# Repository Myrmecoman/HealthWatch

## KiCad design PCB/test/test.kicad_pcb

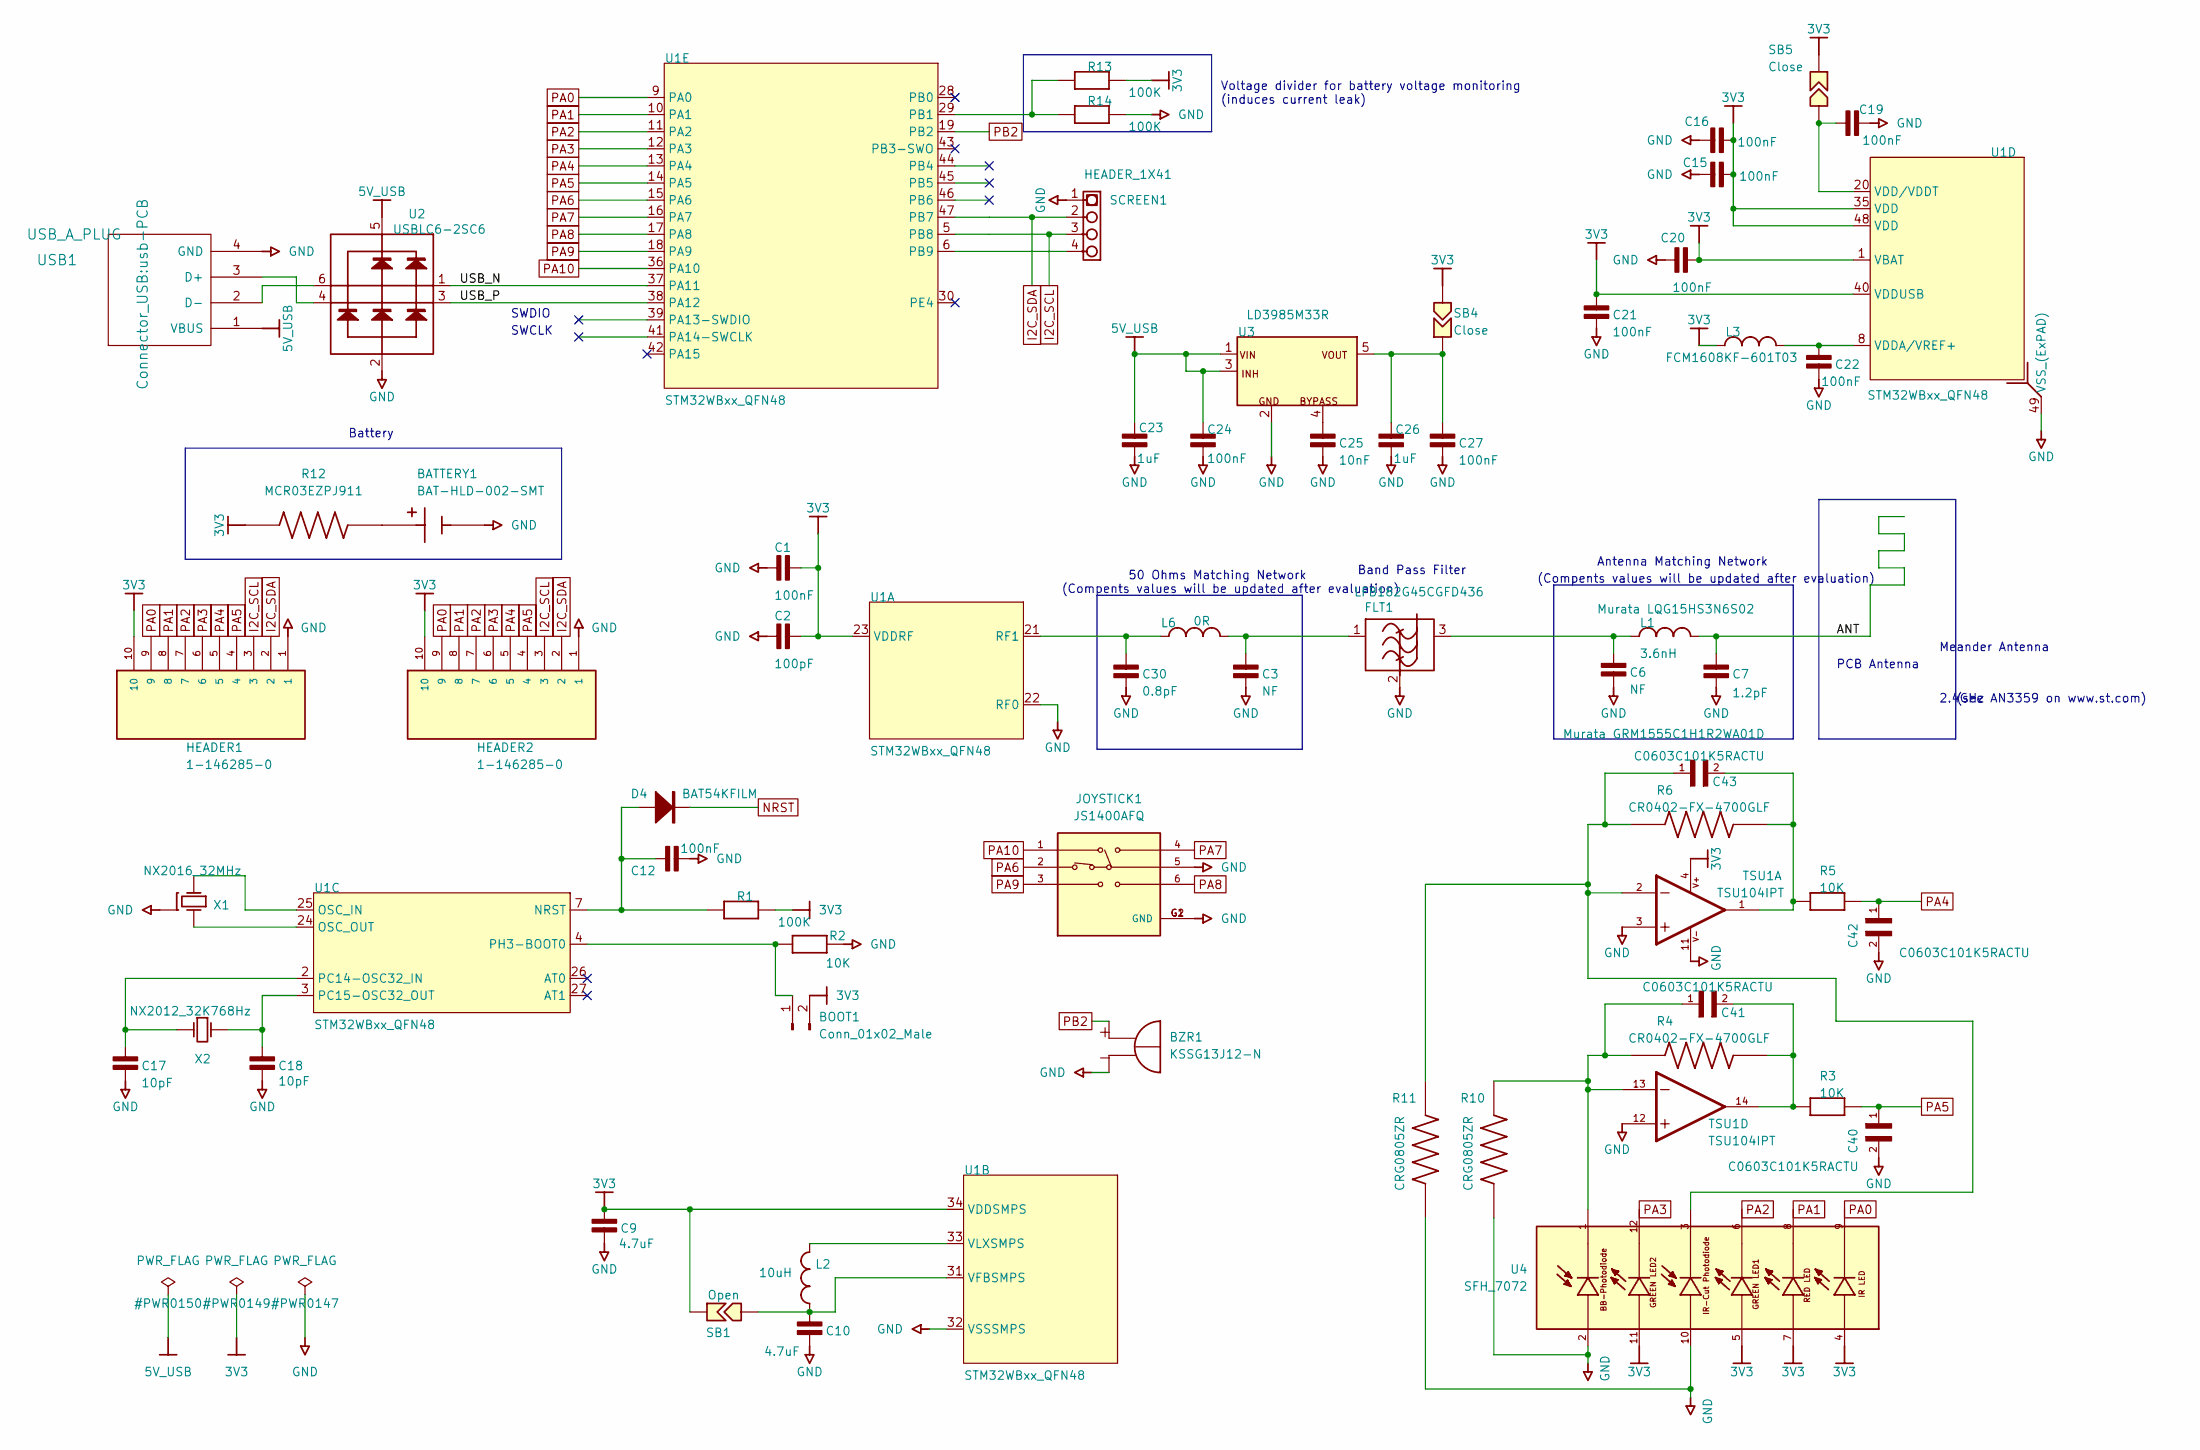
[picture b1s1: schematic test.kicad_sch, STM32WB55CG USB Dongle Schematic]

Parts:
BATTERY1: BAT-HLD-002-SMT; BAT_BAT-HLD-002-SMT; PARTREV B
BOOT1: Conn_01x02_Male; PinHeader_1x02_P2.54mm_Vertical
BZR1: KSSG13J12-N; XDCR_KSSG13J12-N; PARTREV 1.4
C1, C12, C15, C16, C19, C20, C21, C22, C24, C27: 100nF; 0402_CAP_NPOL
C2: 100pF; 0402_CAP_NPOL
C3, C6: NF; 0402_CAP_NPOL
C7: 1.2pF; 0402_CAP_NPOL
C9, C10: 4.7uF; 0402_CAP_NPOL
C17, C18: 10pF; 0402_CAP_NPOL
C23, C26: 1uF; 0603_CAP_NPOL
C25: 10nF; 0402_CAP_NPOL
C30: 0.8pF; 0402_CAP_NPOL
C40, C41, C42, C43: C0603C101K5RACTU; CAPC1608X87N
D4: BAT54KFILM; SOD523
FLT1: LFB182G45CGFD436
HEADER1, HEADER2: 1-146285-0; TE_1-146285-0
JOYSTICK1: JS1400AFQ; SW_JS1400AFQ; PARTREV C
L1: 3.6nH; 0402_COIL
L2: 10uH; 0805_COIL
L3: FCM1608KF-601T03; 0603_COIL
L6: 0R; 0402_COIL
R1, R13, R14: 100K; 0402_RES
R2, R3, R5: 10K; 0402_RES
R4, R6: CR0402-FX-4700GLF; RESC1005X40N
R10, R11: CRG0805ZR; RESC2012X65N; Tolerance 0%; Voltage_Rating 150 V
R12: MCR03EZPJ911; RESC1608X55N
SB1: Open; SB-tiny
SB4, SB5: Close; SB-tiny
SCREEN1: HEADER_1X41; PinHeader_1x04_P2.54mm_Vertical
TSU1: TSU104IPT; SOP65P640X120-14N; PARTREV 3
U1: STM32WBxx_QFN48
U2: USBLC6-2SC6; SOT23-6
U3: LD3985M33R; SOT23-5; MANUFACTURER P/N LD3985M33R
U4: SFH_7072; XDCR_SFH_7072; PARTREV 1.0
USB1: USB_A_PLUG; usb-PCB
X1: NX2016_32MHz; NX2016_4P; MANUFACTURER P/N NX2016SA 32 MHz EXS00A-CS06654
X2: NX2012_32K768Hz; NX2012_2P; MANUFACTURER P/N NX2012SA 32.768KHz EXS00A-MU00389

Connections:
3V3: BOOT1.2, C1.2, C2.2, C9.1, C15.1, C16.1, C20.2, C21.2, HEADER1.10, HEADER2.10, L3.1, R1.1, R12.1, R13.1, SB1.2, SB4.1, SB5.2, TSU1.4, U1.1 (VBAT), U1.23 (VDDRF), U1.34 (VDDSMPS), U1.35 (VDD), U1.40 (VDDUSB), U1.48 (VDD), U4.4, U4.5, U4.7, U4.11
5V_USB: C23.2, C24.2, U2.5, U3.1 (VIN), U3.3 (CE), USB1.1 (VBUS)
/ANT: C7.2, L1.2
/USB_N: U1.37 (PA11), U2.1
/USB_P: U1.38 (PA12), U2.3
GND: BATTERY1.N, BZR1.N, C1.1, C2.1, C3.1, C6.2, C7.1, C9.2, C10.2, C12.2, C15.2, C16.2, C17.2, C18.2, C19.2, C20.1, C21.1, C22.2, C23.1, C24.1, C25.1, C26.1, C27.1, C30.1, C40.2, C42.2, FLT1.2 (GND), HEADER1.1, HEADER2.1, JOYSTICK1.5, JOYSTICK1.G1 (GND), JOYSTICK1.G2 (GND), R2.2, R10.2, R11.2, R14.1, SCREEN1.1, TSU1.3, TSU1.11, TSU1.12, U1.22 (RF0), U1.32 (VSSSMPS), U1.49 (VSS_(ExPAD)), U2.2, U3.2 (VSS), U4.2, U4.10, USB1.4 (GND), X1.2, X1.4
I2C_SCL: HEADER1.3, HEADER2.3, SCREEN1.3, U1.5 (PB8)
I2C_SDA: HEADER1.2, HEADER2.2, SCREEN1.2, U1.47 (PB7)
NRST: D4.K
unnamed: BATTERY1.P1, BATTERY1.P2, R12.2
unnamed: BOOT1.1, R2.1, U1.4 (PH3-BOOT0)
unnamed: C3.2, FLT1.1 (I/O), L6.2
unnamed: C6.1, FLT1.3 (I/O), L1.1
unnamed: C10.1, L2.1, SB1.1, U1.31 (VFBSMPS)
unnamed: C12.1, D4.A, R1.2, U1.7 (NRST)
unnamed: C17.1, U1.2 (PC14-OSC32_IN), X2.1 (OSC1)
unnamed: C18.1, U1.3 (PC15-OSC32_OUT), X2.2 (OSC2)
unnamed: C19.1, SB5.1, U1.20 (VDD/VDDT)
unnamed: C22.1, L3.2, U1.8 (VDDA/VREF+)
unnamed: C25.2, U3.4 (BYPASS)
unnamed: C26.2, C27.2, SB4.2, U3.5 (VOUT)
unnamed: C30.2, L6.1, U1.21 (RF1)
unnamed: C41.1, R4.1, R10.1, TSU1.13, U4.1
unnamed: C41.2, R3.1, R4.2, TSU1.14
unnamed: C43.1, R6.1, R11.1, TSU1.2, U4.3
unnamed: C43.2, R5.1, R6.2, TSU1.1
unnamed: L2.2, U1.33 (VLXSMPS)
unnamed: R13.2, R14.2, U1.29 (PB1)
unnamed: SCREEN1.4, U1.6 (PB9)
unnamed: U1.24 (OSC_OUT), X1.3 (OSC2)
unnamed: U1.25 (OSC_IN), X1.1 (OSC1)
unnamed: U2.4, USB1.3 (D+)
unnamed: U2.6, USB1.2 (D-)
PA0: HEADER1.9, HEADER2.9, U1.9 (PA0), U4.9
PA1: HEADER1.8, HEADER2.8, U1.10 (PA1), U4.8
PA2: HEADER1.7, HEADER2.7, U1.11 (PA2), U4.6
PA3: HEADER1.6, HEADER2.6, U1.12 (PA3), U4.12
PA4: C42.1, HEADER1.5, HEADER2.5, R5.2, U1.13 (PA4)
PA5: C40.1, HEADER1.4, HEADER2.4, R3.2, U1.14 (PA5)
PA6: JOYSTICK1.2, U1.15 (PA6)
PA7: JOYSTICK1.4, U1.16 (PA7)
PA8: JOYSTICK1.6, U1.17 (PA8)
PA9: JOYSTICK1.3, U1.18 (PA9)
PA10: JOYSTICK1.1, U1.36 (PA10)
PB2: BZR1.P, U1.19 (PB2)

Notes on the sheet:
(Compents values will be updated after evaluation)
Band Pass Filter
PCB Antenna
SWDIO
Antenna Matching Network
(see AN3359 on www.st.com)
2.4GHz
50 Ohms Matching Network
SWCLK
Meander Antenna
Battery
Voltage divider for battery voltage monitoring (induces current leak)

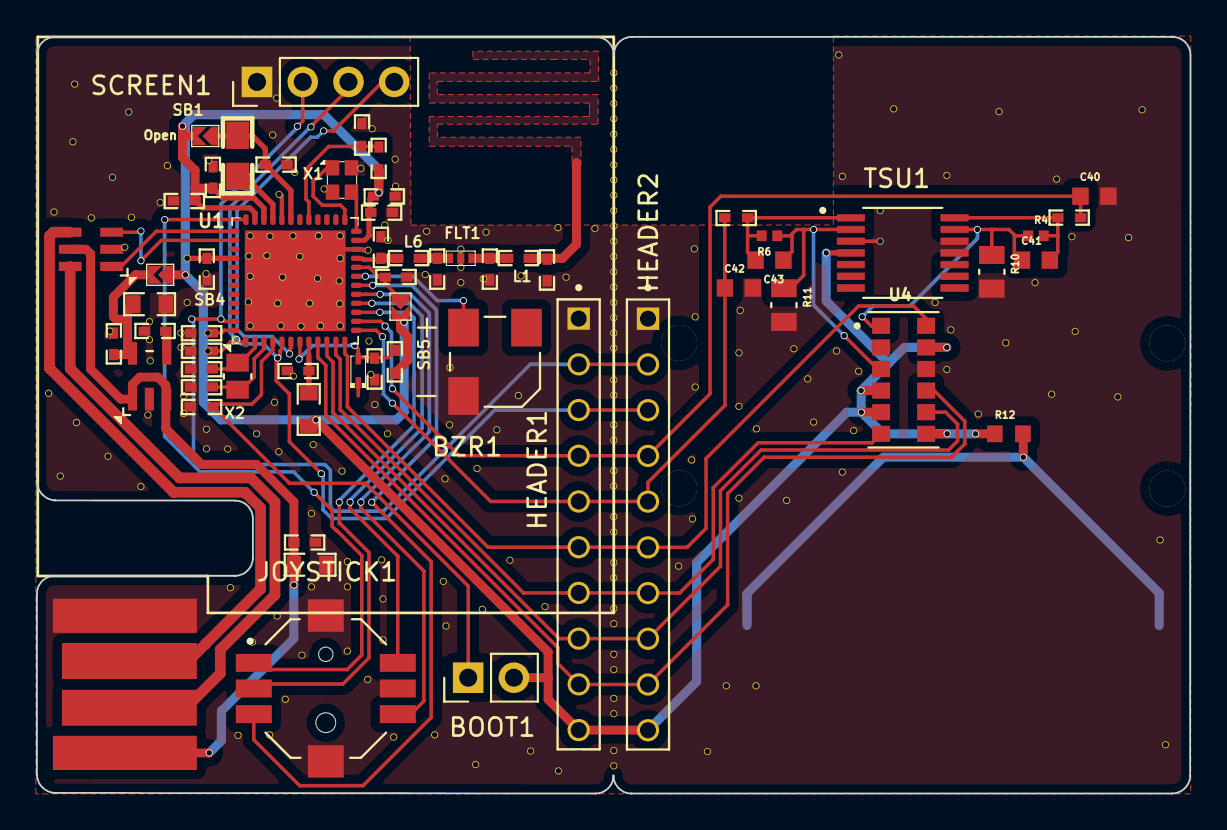
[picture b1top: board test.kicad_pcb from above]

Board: 2 copper layers, 64.1 x 42.0 mm, 61 parts (1 on the bottom side), 44 nets.

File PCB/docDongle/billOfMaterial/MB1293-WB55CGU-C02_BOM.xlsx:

|  |  |  | Bill of materials
 |  |  |  | Board reference: | MB1293
 |  |  |  | Variant: | ---
 |  |  |  | PCB revision: | C
 |  |  |  | Assembly revision: | 02
 |  |  |  | Date: | 14th November 2018
Designator | Description | Comment | FootPrint | Manufacturer | Manufacturer Part_Number | Fitted | Quantity | ECCN_EU | ECCN_US
C1, C12, C15, C16, C19, C20, C21, C22, C24, C27 | Capacitor_not polarized X7R | 100nF | 0402_CAP_NPOL |  |  | YES | 10 | NA | NA
C2 | Capacitor_not polarized | 100pF | 0402_CAP_NPOL |  |  | YES | 1 | NA | NA
C3 | Capacitor_not polarized | --- | 0402_CAP_NPOL |  |  | NO | 1 | NA | NA
C4, C25 | Capacitor_not polarized | 10nF | 0402_CAP_NPOL |  |  | YES | 2 | NA | NA
C8, C28, C29 | Capacitor_not polarized | --- | 0402_CAP_NPOL |  |  | NO | 3 | NA | NA
C6 | Capacitor_not polarized | --- | 0402_CAP_NPOL |  |  | NO | 1 | NA | NA
C7 | Capacitor_not polarized | 1.2pF | 0402_CAP_NPOL | MURATA | GRM1555C1H1R2WA01D | YES | 1 | NA | NA
C9, C10 | Capacitor_not polarized | 4.7uF | 0402_CAP_NPOL |  |  | YES | 2 | NA | NA
C17, C18 | Capacitor_not polarized | 10pF | 0402_CAP_NPOL |  |  | YES | 2 | NA | NA
C23, C26 | Capacitor_not polarized | 1uF | 0603_CAP_NPOL |  |  | YES | 2 | NA | NA
C30 | Capacitor_not polarized | 0.5pF | 0402_CAP_NPOL | MURATA | GRM1555C1HR50BZ01D | YES | 1 | NA | NA
CN1, CN2 | SIL10 2.54mm | HEADER_1X10 | Header M/F 1x10x2.54 NF |  |  | NO | 2 | NA | NA
CN3 | USB Type A Plug SMD | USB_1 | USB/A_M1 | MOLEX | 48037-1000 | YES | 1 | NA | NA
CN4 | SMD connector | HEADER_1X4 | SIL4_127_B |  |  | NO | 1 | NA | NA
CN5 | SMD RF Connector | UFL | UFL | HIROSE | U.FL-R-SMT-1 | YES | 1 | NA | NA
D1 | Light-Emitting Diode | LED BLUE | 0603_LED_Blue | EVERLIGHT | 19-217/BHC-AN1P2/3T | YES | 1 | EAR99 | NEC
D2 | Light-Emitting Diode | LED GREEN | 0603_LED_GREEN | EVERLIGHT | 19-213SYGC/S530-E2/TR8 | YES | 1 | EAR99 | NEC
D3 | Light-Emitting Diode | LED RED | 0603_LED_RED | EVERLIGHT | 19-213/R6C-AP1Q2B/3T | YES | 1 | EAR99 | NEC
D4 | Schottky Diode | BAT54KFILM | SOD523 | ST | BAT54KFILM | YES | 1 | EAR99 | NEC
FLT1 | Band Pass Filter Murata LFB182G45CGFD436 | LFB182G45CGFD436 | LFB182G45CGFD436 | MURATA | LFB182G45CGFD436 | YES | 1 | EAR99 | NEC
U1 | STM32WB55CGU6U | STM32WB55_QFN48 | STM32WB55_QFN48 | ST | STM32WB55CGU6U | YES | 1 | 5A002.A.2 | 5A002.A.2
U2 | ESD protection for USB | USBLC6-2SC6 | SOT23-6 | ST | USBLC6-2SC6 | YES | 1 | EAR99 | NEC
U3 | 3.3V low drop voltage regulator | LD3985M33R | SOT23-5 | ST | LD3985M33R | YES | 1 | EAR99 | NEC
L1 | Coil Murata | 3.6nH | 0402_COIL | MURATA | LQG15HS3N6S02 | YES | 1 | NA | NA
L2 | Coil Wurtz 10uH ref: 74479777310A | 10uH | 0805_COIL | WURTH | 74479777310A | YES | 1 | NA | NA
L3 | Filtering coil | FCM1608KF-601T03 | 0603_COIL | TAI-TECH | FCM1608KF-601T03 | YES | 1 | NA | NA
L4 | zero ohm resistor | 0R | 0402_COIL |  |  | YES | 1 | NA | NA
L6 | zero ohm resistor | 0R | 0402_COIL |  |  | YES | 1 | NA | NA
R1 | Resistor | 100K | 0402_RES |  |  | YES | 1 | NA | NA
R2 | Resistor | 10K | 0402_RES |  |  | YES | 1 | NA | NA
R3 | Resistor | 1K | 0402_RES |  |  | YES | 1 | NA | NA
R4, R5, R6 | Resistor | 680 | 0402_RES |  |  | YES | 3 | NA | NA
SB1, SB3, SB6 | Solder Jumper | Open | SB-tiny | --- | --- | NO | 3 | NA | NA
SB2, SB4, SB5 | Solder Jumper | Close | SB-tiny | --- | --- | YES | 3 | NA | NA
SC1, SC2, SC3, SC4 | Harwin S0951-46R | Shield Clip_A 3.9x1.1x1.28 | Shield Clip_A 3.9x1.1x1.28 | Harwin | S0951-46R | YES | 4 | NA | NA
SH1 | Shield | Shield 17.2x17.2x3 | Shield 17.2x17.2x3 | ST custom | See decription | YES | 1 | NA | NA
STICKER_1 | Sticker for FCC_ID 16x5mm Placed on top of Shield | FCC_ID_Sticker_16x5 | Sticker_FCC_ID 16x5mm | Subcontractor | --- | YES | 1 | NA | NA
STICKER_2 | Sticker BoardRef 21x5mm | Sticker_Prod_21x6 | Sticker_Prod_21x5mm | Subcontractor | --- | YES | 1 | NA | NA
SW1 | Push-button SMD | User PB | SW-PB SMD KMR2 | C&K | KMR231GLFS | YES | 1 | NA | NA
SW2 | Switch 1RT | MLL1200S_TE | MLL1200S_TE | TE | MLL1200S | YES | 1 | NA | NA
X1 | Crystal NDK 2.0x1.6mm 32 MHz | NX2016_32MHz | NX2016_4P | NDK | EXS00A-CS06654 (ESX10B-18811D) | YES | 1 | NA | NA
X2 | Crystal NDK 2.0x1.2mm 32.768 KHz | NX2012_32K768Hz | NX2012_2P | NDK | EXS00A-MU00389 (EXS11B-04659) | YES | 1 | NA | NA
PCB | PCB | PCB 1.6mm 2Layers FR4 #50.5 x 26.2 mm Solder_Mask = BLUE Silkscreen = White | MB1293C | Subcontractor | ---- | YES | 1 | NA | NA

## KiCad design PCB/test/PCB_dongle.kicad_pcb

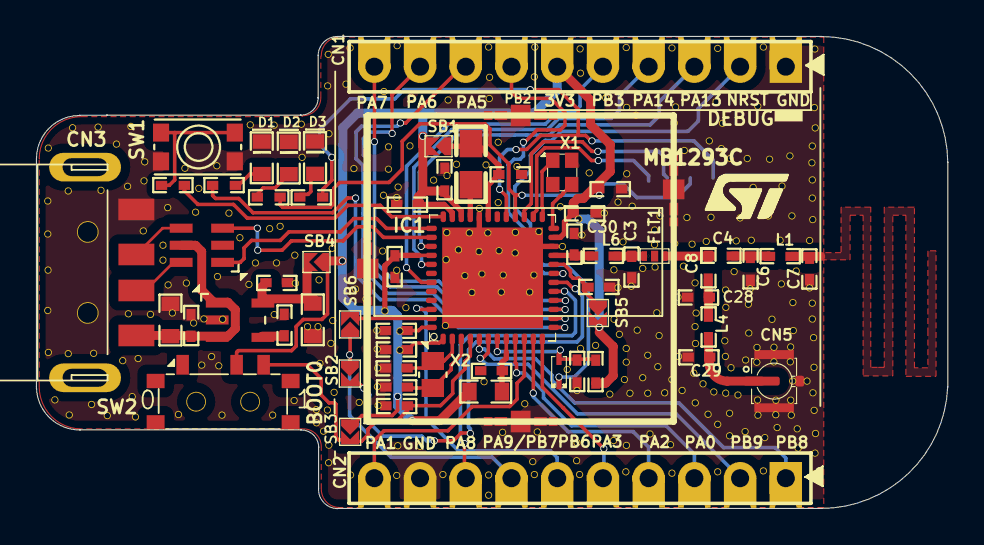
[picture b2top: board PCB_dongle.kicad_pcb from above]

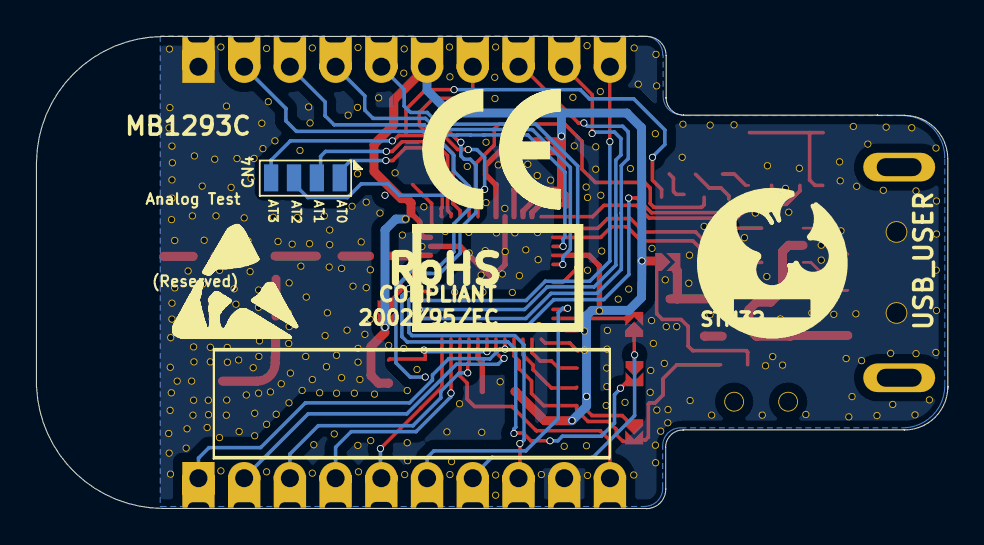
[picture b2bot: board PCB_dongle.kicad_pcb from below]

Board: 2 copper layers, 50.6 x 26.2 mm, 73 parts (7 on the bottom side), 55 nets.

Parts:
C1, C12, C15, C16, C19, C20, C21, C22, C24, C27: 100nF; 0402_CAP_NPOL
C2: 100pF; 0402_CAP_NPOL
C3: 0.3pF; 0402_CAP_NPOL
C4, C25: 10nF; 0402_CAP_NPOL
C6, C8, C28, C29: NF; 0402_CAP_NPOL
C7: 1.5pF; 0402_CAP_NPOL
C9, C10: 4.7uF; 0402_CAP_NPOL
C17, C18: 10pF; 0402_CAP_NPOL
C23, C26: 1uF; 0603_CAP_NPOL
C30: 0.8pF; 0402_CAP_NPOL
CN1, CN2: HEADER_1X10; Header M{slash}F 1x10x2.54 NF
CN3: USB_1; USB{slash}A_M1
CN4: HEADER_1X4; SIL4_127_B
CN5: UFL
D1: LED BLUE; 0603_LED_Blue
D2: LED GREEN; 0603_LED_GREEN
D3: LED RED; 0603_LED_RED
D4: BAT54K; SOD523
FLT1: LFB182G45CGFD436
IC1: STM32WBxx_QFN48
IC2: USBLC6-2; SOT23-6
L1: 3.6nH; 0402_COIL
L2: 10uH; 0805_COIL
L3: FCM1608KF-601T03; 0603_COIL
L4: 0R; 0402_COIL
L6: 2.7nH; 0402_COIL
Label_1: LOGO_ST; LOGO_ST_Size2
Label_2: LOGO_ROHS; SYMBOL_RoHS
Label_3: LOGO_StickerArea_Prod_Reservation; LOGO_Sticker_Area
Label_4: LOGO_STM32
Label_6: LOGO_CE; LOGO CE
Label_7: LOGO_ESD; LOGO ESD
R1: 100K; 0402_RES
R2: 10K; 0402_RES
R3: 1K; 0402_RES
R4, R5, R6: 680; 0402_RES
SB1, SB3, SB5, SB6: Open; SB-tiny
SB2, SB4: Close; SB-tiny
SC1, SC2, SC3, SC4: Shield Clip_A 3.9x1.1x1.28
SH1: Shield 17.2x17.2x3; SHIELD 17.2X17.2X3
STICKER_1: FCC_ID_Sticker_16x6; Sticker_FCC_ID 16x6mm
STICKER_2: Sticker_Prod_22x6; Sticker_Prod_22x6mm
SW1: User PB; SW-PB SMD KMR2
SW2: MLL1200S_TE
U1: LD3985M33R; SOT23-5
X1: NX2016_32MHz; NX2016_4P
X2: NX2012_32K768Hz; NX2012_2P

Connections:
3V3: C1.2, C2.2, C9.1, C15.1, C16.1, C20.2, C21.2, CN1.6, IC1.1, IC1.23, IC1.34, IC1.35, IC1.40, IC1.48, L3.1, R1.1, SB1.2, SB3.1, SB4.1, SB5.2, SW2.2
5V_USB: C23.2, C24.2, CN3.1, IC2.5, U1.1, U1.3
ANT: C7.2, L1.2
BOOT0: IC1.4, R2.1, SB3.2, SW2.3
GND: C1.1, C2.1, C3.1, C6.2, C7.1, C9.2, C10.2, C12.2, C15.2, C16.2, C17.2, C18.2, C19.2, C20.1, C21.1, C22.2, C23.1, C24.1, C25.1, C26.1, C27.1, C28.2, C29.2, C30.1, CN1.1, CN2.9, CN3.0, CN3.4, CN5.2, D1.K, D2.K, D3.K, FLT1.2, IC1.22, IC1.32, IC1.49, IC2.2, R2.2, SC1.1, SC2.1, SC3.1, SC4.1, SW1.1, U1.2, X1.2, X1.4
NRST: CN1.2, D4.K
NetC3_2: C3.2, FLT1.1, L6.2
NetC4_1: C4.1, C8.1, FLT1.3
NetC4_2: C4.2, C6.1, L1.1
NetC8_2: C8.2, C28.1, L4.1
NetC10_1: C10.1, IC1.31, L2.1, SB1.1
NetC12_1: C12.1, D4.A, IC1.7, R1.2
NetC17_1: C17.1, IC1.2, X2.1
NetC18_1: C18.1, IC1.3, X2.2
NetC19_1: C19.1, IC1.20, SB5.1
NetC22_1: C22.1, IC1.8, L3.2
NetC25_2: C25.2, U1.4
NetC26_2: C26.2, C27.2, SB4.2, U1.5
NetC29_1: C29.1, CN5.1, L4.2
NetC30_2: C30.2, IC1.21, L6.1
NetCN2_7: CN2.7, SB2.1, SB6.1
NetCN3_2: CN3.2, IC2.6
NetCN3_3: CN3.3, IC2.4
NetCN4_1: CN4.1, IC1.26
NetCN4_2: CN4.2, IC1.27
NetD1_A: D1.A, R4.2
NetD2_A: D2.A, R5.2
NetD3_A: D3.A, R6.2
NetIC1_24: IC1.24, X1.3
NetIC1_25: IC1.25, X1.1
NetIC1_33: IC1.33, L2.2
NetR3_1: R3.1, SW1.2
PA0: CN2.3, IC1.9
PA1: CN2.10, IC1.10
PA2: CN2.4, IC1.11
PA3: CN2.5, IC1.12
PA4: IC1.13, R4.1
PA5: CN1.8, IC1.14
PA6: CN1.9, IC1.15
PA7: CN1.10, IC1.16
PA8: CN2.8, IC1.17
PA9: IC1.18, SB2.2
PA10: IC1.36, R3.2
PA13: CN1.3, IC1.39
PA14: CN1.4, IC1.41
PB0: CN4.3, IC1.28, R5.1
PB1: CN4.4, IC1.29, R6.1
PB2: CN1.7, IC1.19
PB3: CN1.5, IC1.43
PB6: CN2.6, IC1.46
PB7: IC1.47, SB6.2
PB8: CN2.1, IC1.5
PB9: CN2.2, IC1.6
USB_N: IC1.37, IC2.1
USB_P: IC1.38, IC2.3

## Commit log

2022-04-13 initialisation du projet
2022-04-30 dongle model
2022-04-30 adding prototype model
2022-05-03 updating 3D models
2022-05-10 préparation pour affichage écran
2022-05-11 code test écran et boutons
2022-05-16 code avec oxymètre
2022-05-17 better code for oxymeter
2022-06-15 adding pcb data
2022-06-15 feat(proto): add proto codebase
2022-06-19 adding dip files
2022-06-28 ajout du sch kicad
2022-06-28 ajout de test
2022-06-28 ajout buzzer + oxymètre
2022-06-29 schema quasi fini
2022-06-29 suppression pins
2022-06-29 changement nrst
2022-06-29 génération netlist
2022-07-12 ajout de footprints
2022-07-12 import pcb réussis, quelques erreurs encore (voir report.txt)
2022-07-13 ajout pcb dongle pour comparaison
2022-07-16 ajout usb
2022-07-16 ajout de l'usb dans le pcb
2022-07-28 avancées pcb
2022-07-28 pcb v1, il faut encore connecter les gnd
2022-07-29 ajout gnd zone, il faut encore mettre les pads
2022-07-29 modif sur la gnd zone
2022-07-31 nouveaux boutons, réduction taille
2022-08-01 correction d'erreurs + compacité
2022-08-02 fix d'une erreur
2022-08-02 Revert "fix d'une erreur"
    This reverts commit d237dfa0d90c399318c3ec0f34094da9eb165235.
2022-08-02 réduction taille des routes
2022-08-02 ajout des grounds
2022-08-03 fix through hole gnd
2022-08-03 small error fixes
2022-08-05 fixed issues + drill centroid
2022-08-05 ajout titre
2022-08-05 changement bom
2022-08-18 suppression du bouton boot + pcb usb
2022-08-18 changement oxymètre
2022-08-22 beaucoup de changements
2022-08-22 ajout ampliop capteur, reste UVNC et 10x pin header
2022-08-22 ajout headers, reste circuit + UVNC
2022-08-23 filtres
2022-08-24 nettoyage routes et gnd
2022-08-27 réduction taille
2022-08-30 améliorations circuits, remplacement SFH7060 etc
2022-08-31 ajout pin monitoring pile
2022-08-31 changement coté silkscreen
2022-09-02 ajout alim TSU104
2022-10-22 ajout i2c
2022-10-24 ajout 4 trous
2022-11-07 update files
2022-11-29 améliorations pcb
2022-12-07 update pcb
2022-12-15 changement cables USB vers transimpédance de 120 ohms
2022-12-15 écartement antenne
